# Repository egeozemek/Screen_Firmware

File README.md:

# Tympanometer

A low-cost tympanometer designed to diagnose hearing loss in children, developed as part of the [Duke BME Design Fellows](https://bme.duke.edu/academics/undergrad/design-fellows/) program at Duke University's Pratt School of Engineering under the supervision of [Dr. Mark Palmeri, MD PhD](https://github.com/mlp6).

- [Duke BME Designers Develop a New Tool to Inexpensively Diagnose Hearing Loss in Children](https://pratt.duke.edu/news/duke-bme-designers-develop-a-new-tool-to-inexpensively-diagnose-hearing-loss-in-children/)
- [Preventing Childhood Hearing Loss Worldwide](https://pratt.duke.edu/news/preventing-childhood-hearing-loss-worldwide/)

---

## Team

**Iris Ye** · **Alisha Gupta** · **James Mu**

---

## Repository Structure

This repo has three active branches, one per contributor:

| Branch | Owner | Focus |
|--------|-------|-------|
| `main` | James Mu | Firmware, OLED display integration, microphone PCB |
| *(Alisha's branch)* | Alisha Gupta | Audio/microphone analog circuit PCB |
| *(Iris's branch)* | Iris Ye | Isolated microphone PCB and analog filtering |

---

## What We've Built

### Firmware & OLED Display — James Mu

Integrated a GME12864-13 (128×64 SSD1306) OLED display into the device running on the nRF52833 DK under Zephyr RTOS. The display renders a real-time tympanogram trace with a split-zone layout:

- **Yellow zone (rows 0–15):** ear canal volume (ECV), static admittance (SA), and peak pressure (PPP)
- **Blue zone (rows 16–63):** tympanogram curve plotted from −400 to +200 daPa

The firmware supports all five standard tympanogram curve types (A, As, Ad, B, C) and currently uses physiologically accurate simulated data. Real ADC input will replace the simulation when the analog front-end is complete.

A custom 3×5 bitmap font is used to minimize flash footprint.

**Hardware:**
- MCU: nRF52833 DK
- Display: GME12864-13 OLED (SSD1306, I2C at 0x3C)
- I2C pins: SDA → P0.27, SCL → P0.26

### Analog Circuitry — Alisha Gupta & Iris Ye

First-iteration PCB designs for the microphone and audio signal chain, focused on filtering out 60 Hz noise from the microphone signal. The team has been exploring different analog filter architectures (including a notch filter redesign) to isolate the tympanometry probe tone from interference.

Key components include:
- **LM4875MM** audio amplifier (SOP-8)
- **TLV313IDBVT** op-amps (×2, TSOT-23-5) for active filtering
- 0603 SMD passive components throughout

A full bill of materials is in [`audio_and_microphone/BOM.csv`](audio_and_microphone/BOM.csv).

---

## Build & Flash (Firmware)

```bash
west build -b nrf52833dk/nrf52833
west flash
```

Requires a [Zephyr RTOS](https://docs.zephyrproject.org/) environment set up with the nRF Connect SDK.

---

*This README was drafted with the assistance of Claude (Anthropic) based on information provided by the team.*

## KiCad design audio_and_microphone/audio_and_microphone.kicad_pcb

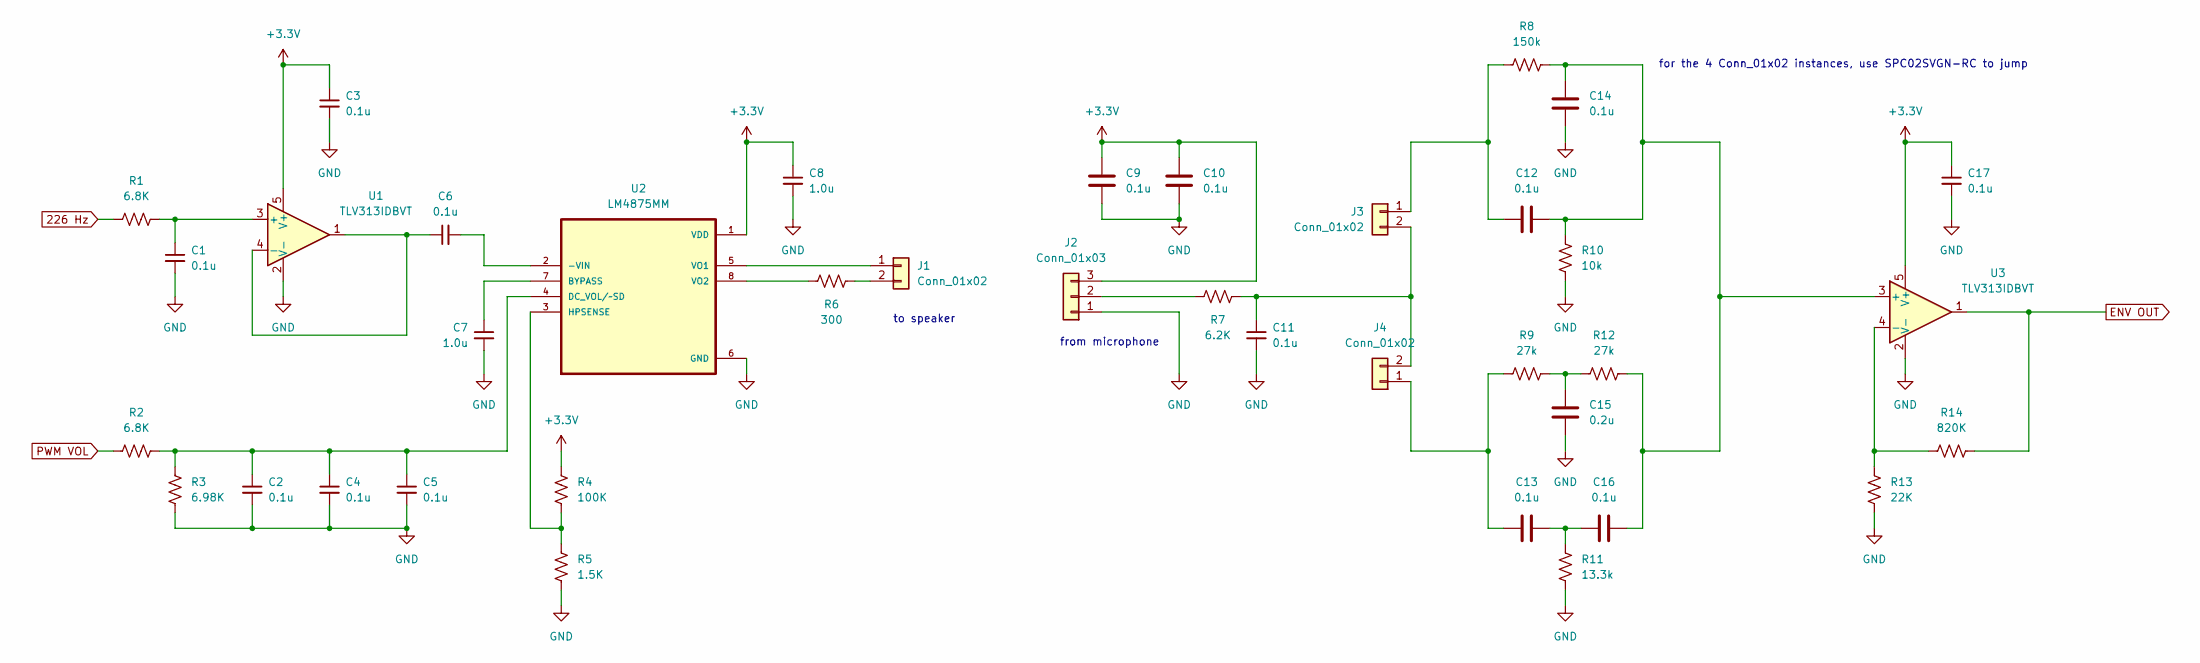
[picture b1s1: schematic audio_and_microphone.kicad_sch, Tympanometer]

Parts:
C1, C2, C3, C4, C5, C6, C9, C10, C11, C12, C13, C14, C16, C17: 0.1u; CAPC17595_95N_KEM-M
C7, C8: 1.0u; CAPC17595_95N_KEM-M
C15: 0.2u; CAPC17595_95N_KEM-M
J1, J3, J4: Conn_01x02; PinHeader_1x02_P2.54mm_Vertical
J2: Conn_01x03; PinHeader_1x03_P2.54mm_Vertical
R1, R2: 6.8K; RC0603N_YAG-M
R3: 6.98K; RC0603N_YAG-M
R4: 100K; RC0603N_YAG-M
R5: 1.5K; RC0603N_YAG-M
R6: 300; RC0603N_YAG-M
R7: 6.2K; RC0603N_YAG-M
R8: 150k; RC0603N_YAG-M
R9, R12: 27k; RC0603N_YAG-M
R10: 10k; RC0603N_YAG-M
R11: 13.3k; RC0603N_YAG-M
R13: 22K; RC0603N_YAG-M
R14: 820K; RC0603N_YAG-M
U1, U3: TLV313IDBVT; TSOT-23-5
U2: LM4875MM; SOP65P490X110-8N

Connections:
226 Hz: R1.2; also elsewhere on the board
+3.3V: C3.1, C8.1, C9.2, C10.2, C17.1, J2.3, R4.1, U1.5 (V+), U2.1 (VDD), U3.5 (V+); also elsewhere on the board
ENV OUT: R14.1, U3.1; also elsewhere on the board
GND: C1.2, C2.2, C3.2, C4.2, C5.2, C7.2, C8.2, C9.1, C10.1, C11.2, C14.2, C15.2, C17.2, J2.1, R3.2, R5.2, R10.2, R11.2, R13.2, U1.2 (V-), U2.6 (GND), U3.2 (V-); also elsewhere on the board
unnamed: C13.2, C16.2, R11.1
unnamed: C15.1, R9.2, R12.1
unnamed: J1.1, U2.5 (VO1)
unnamed: J1.2, R6.1
unnamed: J2.2, R7.2
unnamed: C12.1, J3.1, R8.1
unnamed: C11.1, J3.2, J4.2, R7.1
unnamed: C13.1, J4.1, R9.1
unnamed: C1.1, R1.1, U1.3 (+)
unnamed: C6.1, U1.1, U1.4 (-)
unnamed: C6.2, U2.2 (-VIN)
unnamed: C7.1, U2.7 (BYPASS)
unnamed: C2.1, C4.1, C5.1, R2.1, R3.1, U2.4 (DC_VOL/~SD)
unnamed: R4.2, R5.1, U2.3 (HPSENSE)
unnamed: R6.2, U2.8 (VO2)
unnamed: C12.2, C14.1, C16.1, R8.2, R10.1, R12.2, U3.3 (+)
unnamed: R13.1, R14.2, U3.4 (-)
PWM VOL: R2.2; also elsewhere on the board

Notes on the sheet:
for the 4 Conn_01x02 instances, use SPC02SVGN-RC to jump
to speaker
from microphone

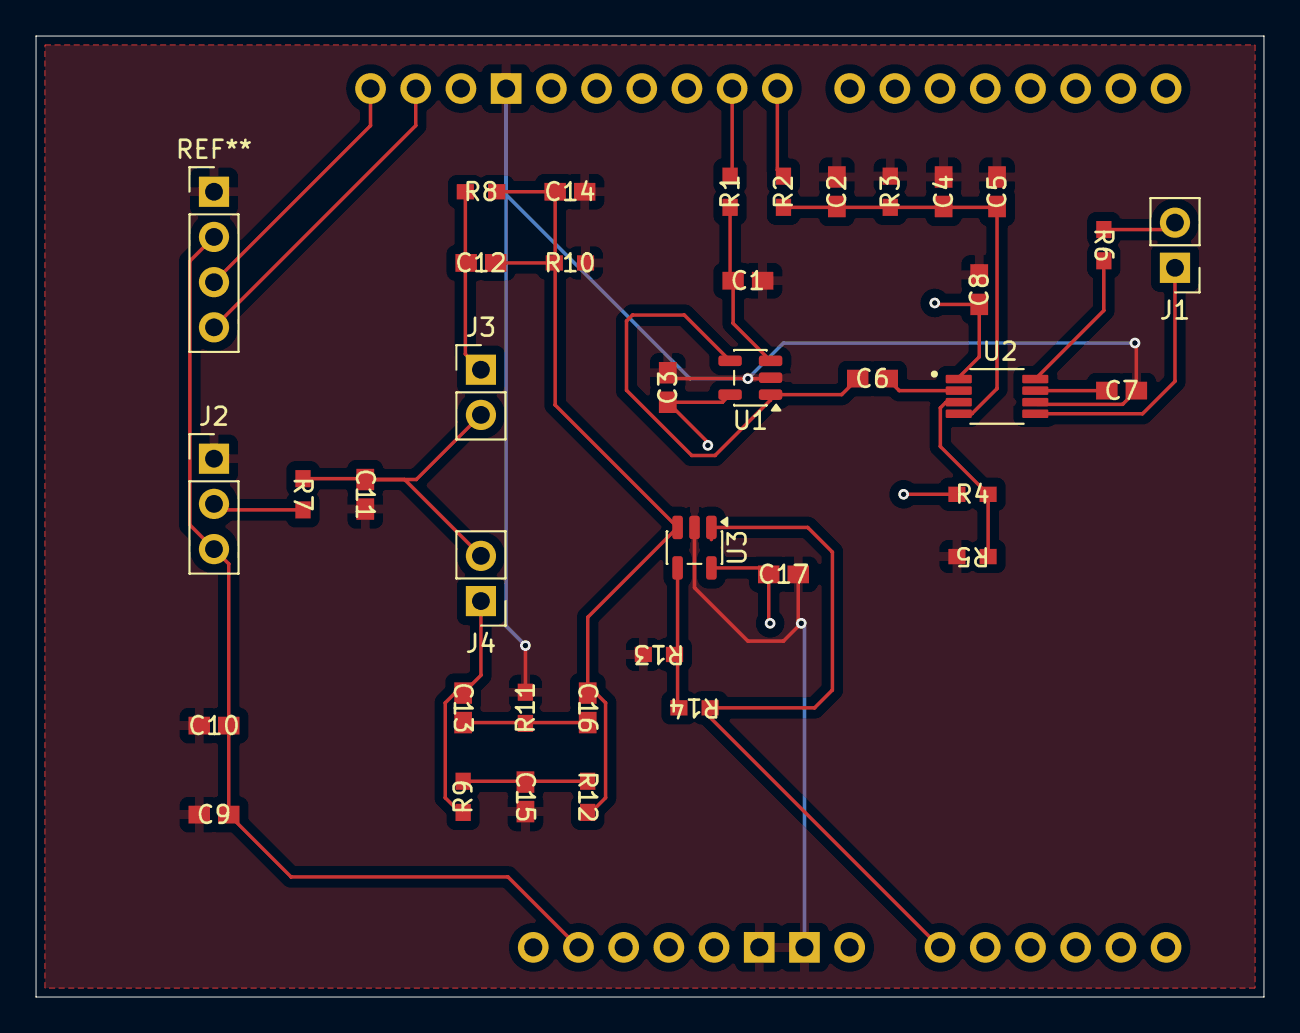
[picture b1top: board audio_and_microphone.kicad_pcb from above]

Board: 2 copper layers, 69.0 x 54.0 mm, 39 parts (0 on the bottom side), 22 nets.

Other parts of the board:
A**: Arduino_Uno_R3_Shield

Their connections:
226 Hz: A**.P0.19; also elsewhere on the board
+3.3V: A**.VDD; also elsewhere on the board
ENV OUT: A**.P0.03; also elsewhere on the board
GND: A**.GND; also elsewhere on the board
PWM VOL: A**.P0.17; also elsewhere on the board

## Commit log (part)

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2026-01-16 init readme for fun
2026-01-20 init OLED testing
2026-01-21 uploaded mic schematics
2026-01-21 Iris' redesign tympanometer schedmatic design
2026-01-21 moving sine wave
2026-01-21 updated shcematics after meeting 1/21/26
2026-01-21 integrated VPWL for microphone testing
2026-01-26 1/26 edit SPICE modeling
2026-01-26 updated schematic to use compliance data for simulation
2026-01-28 notch filter redesign 1/28
2026-01-28 new update 1/28/26 with simulation
2026-01-28 redesigned notch filter for microphone
2026-02-09 cleaned filed to merge microphone and audio schematics into audio_and_microphone schematic
2026-02-09 updated gitignore file
2026-02-09 updated notch filter on microphone
2026-02-09 updated audio and microphone circuit with new redesigned notch filter that was lost
2026-02-11 Remove KiCad backup/temp files from tracking and update .gitignore
2026-04-03 crop photo
2026-06-03 Overlay for 2.42 (turn off I2C, adjust pins)
2026-06-03 proj.conf for new screen
2026-06-04 SPI working on safe GPIO pins (P0.04 + A header pins)
2026-06-04 State Machine Diagram Version 1
2026-06-06 Designs for Screen Pages
2026-06-07 Added display.h and Completed bring-up portion of display.c
2026-06-07 Fixed display.c
2026-06-07 Results Screen
2026-06-07 Dispatcher Done
2026-06-07 Dispatcher Fixed
2026-06-07 Auto-Pager (Claude)
2026-06-07 display.h first version
2026-06-07 Added new charachters
2026-06-07 Fixed bugs in display.c and display.h
2026-06-07 Added display.c to CMakeLists.txt
2026-06-07 Test Harness by Claude
2026-06-07 Bugs fixed _ Test Data Working
2026-06-07 Designs for angle (tilt) screen
2026-06-07 display.c edits for tilt (angle)
2026-06-08 Added angle screen to main.c, fixed display.c
2026-06-08 nrf52833dk_nrf52833.overlay
2026-06-08 Fixed errors in display.c and display.h for pins 1.01-1.05 configuration
